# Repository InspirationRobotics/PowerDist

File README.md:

# PowerDist

`kicad` holds the kicad project / gerber files for the board, and `Power_dist` holds the code running on the microcontroller that actually does the 
hot-swapping.

The [BOM](https://docs.google.com/spreadsheets/d/1eEv6u52QYOC_kODey6bpNA8GYwr_zVqGhBdzeqPN1tI/edit?usp=sharing) holds all the internal component references 
that are in the kicad project i.e. component '1,1' is a 102k 0603 resistor. 

The [datasheet](https://docs.google.com/document/d/1oroizqdIsIZM1mA43HTIwGpKUFsHDlDQZaLfoY1nW0c/edit) for the board holds some useful information about the 
board capabilities and issues.

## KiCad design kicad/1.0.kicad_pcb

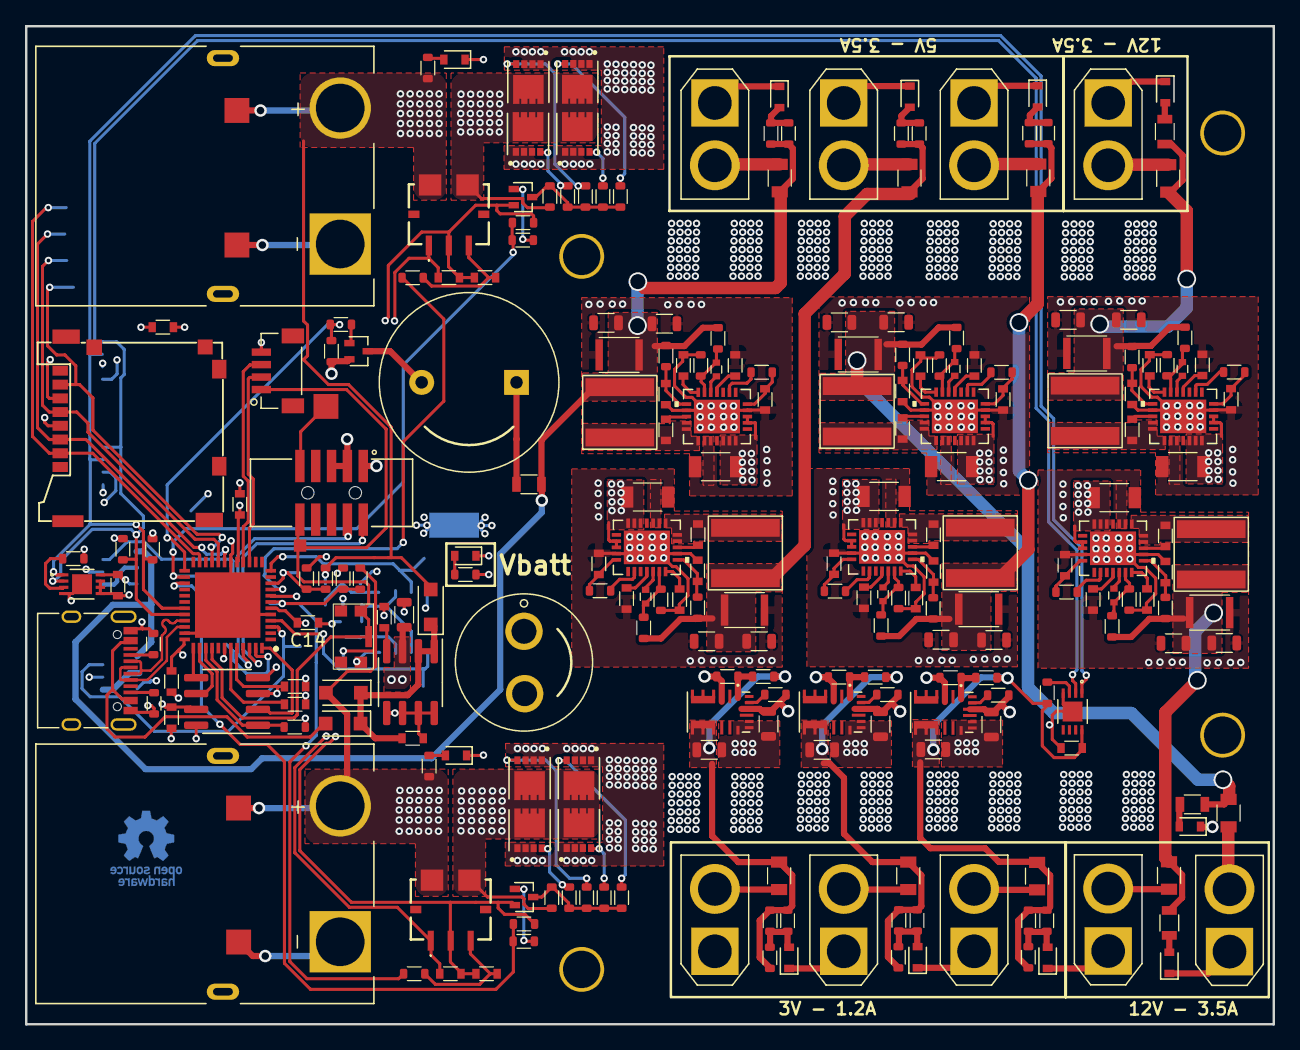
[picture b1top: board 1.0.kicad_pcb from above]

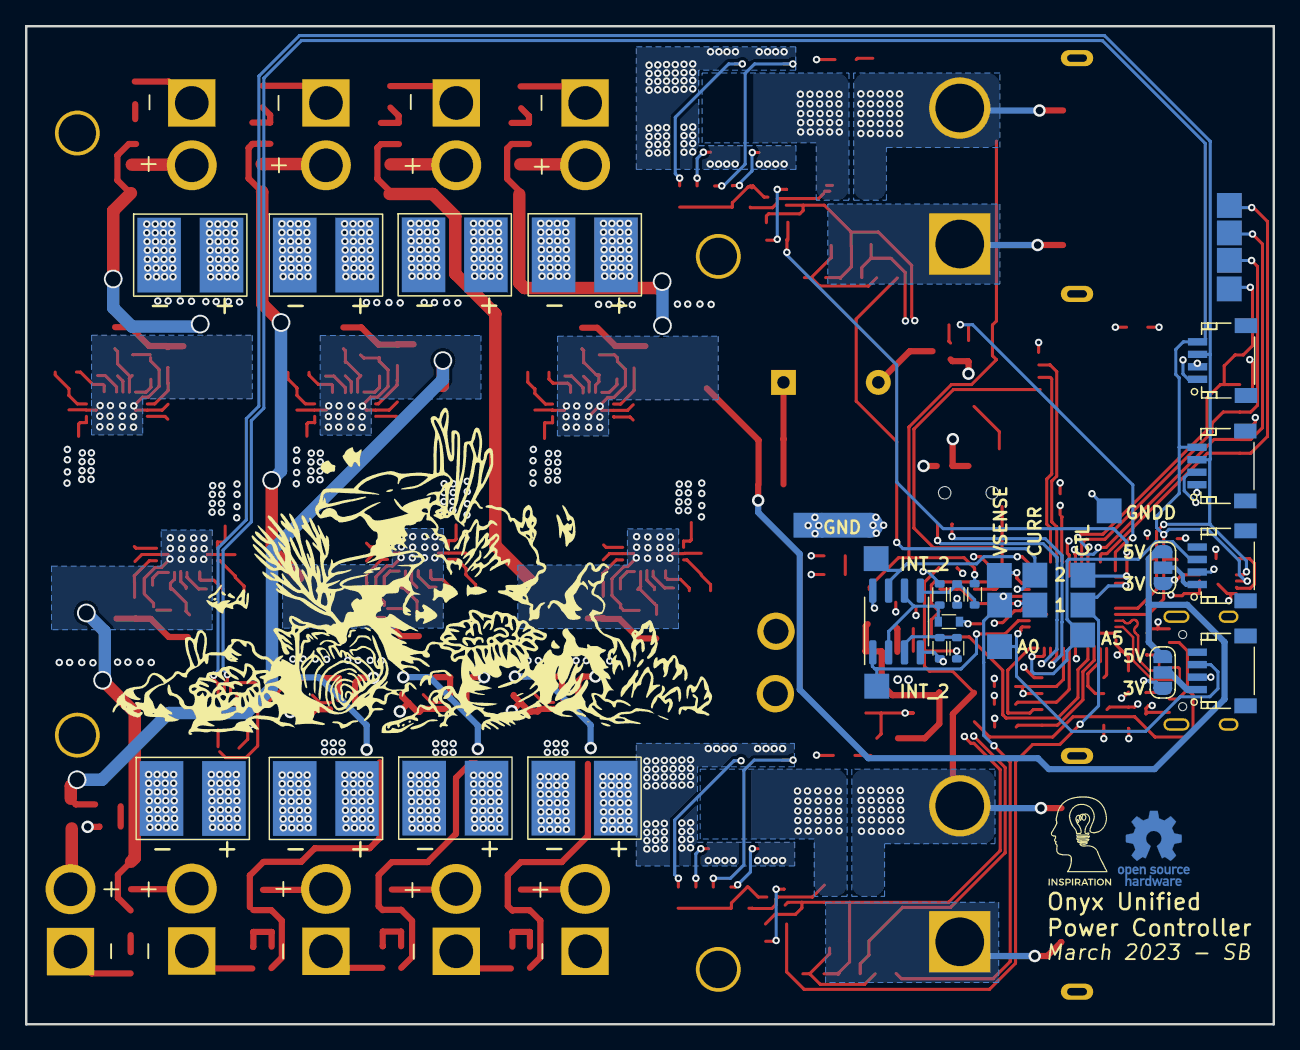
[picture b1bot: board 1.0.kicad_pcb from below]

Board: 4 copper layers, 100.0 x 80.0 mm, 290 parts (39 on the bottom side), 157 nets.

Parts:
C1, C3, C7, C9, C10, C14, C17, C29, C30, C32, C35, C37, C38, C41, C43, C65, C66, C67, C68, C69, C72, C81: 0.1u; C_1608_603_B
C2, C4, C8, C33: 1u; C_1608_603_B
C5: 470u; THT_470uF_Cap
C6, C21, C42, C47, C52, C58: 22u; C_3225_1210_B
C11, C12, C13, C15, C16, C20, C22, C26, C48, C50, C51, C56, C57, C74, C75, C80: 10u; C_2012_805_B
C18, C19, C24, C53, C54, C55: 4u7; C_3216_1206_A
C23, C25, C28, C59, C60, C61: 2u2; C_1608_603_B
C27, C31, C36, C62, C63, C64: 5n6; C_1608_603_B
C34: 100p; C_1608_603_B
C39, C40, C45, C70, C71, C73: OPEN; C_1005_402_A
C44, C46, C49: 47u; C_2012_805_B
D1, D2, D12: D_Schottky; D_SOD-123F
D3, D4, D5, D6, D7, D8, D9, D10, D11, D14, D15, D16: LED; D_0603
F1, F2, F3, F4, F5, F6, F7, F8, F9: Polyfuse_Small; R_2012_805_A
IC1: GD25Q16CWIGR; SOIC-8_3.9x4.9mm_P1.27mm
IC2: ATSAMD21G18A-MUT; QFN50P700X700X90-49N-D
J1: header_01x04; Stemma_QT_V
J3, J4, J5, J6: header_01x04; Stemma_QT_2
J7: uSDCard; uSDCard_SD_503182_011
JP1, JP2: Jumper_NO_Dual; SolderJumper-3_P1.3mm_Open_RoundedPad1.0x1.5mm_NumberLabels
L1, L2, L3: 6u8; XGL6060
L4, L5, L6: 15u; XGL6060
NT1: net-tie; NetTie-2_SMD_Pad2.0mm
P7: CONN_1; OSHW-Logo_5.7x6mm_Copper
Q1, Q2, Q7: Q_NMOS_GSD; SOT-323FL
Q3, Q4, Q5, Q6, Q9, Q10, Q11, Q12: PMOS_SGD; VDFN-8
R1, R2, R4, R6, R23, R48, R49, R53, R67, R80, R82, R84, R90, R92, R94: 10k; R_1608_603_B
R3, R52, R73, R81, R83, R85, R99: 40k2; C_1608_603_B
R5, R9, R15: 470; R_1608_603_B
R7, R18, R20, R24, R26, R50, R97, R98: 4k7; R_1608_603_B
R8, R10: 5k1; R_1608_603_B
R11, R27, R74, R77, R79, R96: 28k; R_1608_603_B
R12, R13, R14, R21, R22, R28, R54, R55, R56, R57: 1k; R_1608_603_B
R16, R25, R38, R39, R40, R41, R42, R43, R44, R45, R46, R47, R58, R59, R60, R61, R62, R63: 300; R_1608_603_B
R17, R19: 22k; R_1608_603_B
R29, R30, R31: 75k; R_1608_603_B
R32, R34, R36: 102k; R_1608_603_B
R33, R35, R37: 32.4k; R_1608_603_B
R51, R68, R69, R70: 500; R_2012_805_B
R66, R71, R75, R86, R87, R88: 4.7; R_1608_603_B
R72, R76, R78: 127k; R_1608_603_B
R89, R91, R93: 124k; R_1608_603_B
SP1: buzzer; 13-9mm_Buzzer
SW1: SW_Push; KMR243GLFG
TP1: TEST; test_point_1.0mm_square
TP2, TP3, TP4, TP5, TP6, TP7, TP8, TP9, TP10, TP11, TP12, TP13, TP14, TP15, TP16, TP17, TP18, TP19, TP20, TP21, TP22: TEST; test_point_2mm_square
U1: ARM-SWD-10
U2, U3: ACS781; 7-LR-PSOF
U4, U5, U6: MPM3610; 20-PowerLQFN
U7, U8, U27, U28: Mounting-holes; plated_hole_3.0x3.6mm
U9, U11, U12, U29, U30, U31: MAX17573; 24_WFQFN
U10: USB_C_2.0; USB_C_XKB_U262-16XN-4BVC11
U13, U14: PCT2075; PCT2075TP_147
U15, U16: XT90PW-M; AMASS_XT90PW-M_Horizontal
U17, U18, U19, U20, U21, U22, U23, U24, U25: XT30_V; AMASS_XT30U-F_1x02_P5.0mm_Vertical
U26, U32, U33, U35, U36, U37, U38, U39: ESC_CONN; 5x3.5x2mm_smd_pad
U34: AP2213-8_SOIC; SOIC-8_3.9x4.9mm_P1.27mm
U42: SOIC-8_3.9x4.9mm_P1.27mm

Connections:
3-3V_1: C15.2, C29.2, F1.2, R32.1, R38.1, R39.1, R40.1, R48.2, U4.9 (OUT), U13.8 (VCC)
3-3V_2: C16.2, F2.2, R34.1, R41.1, R42.1, R43.1, U5.9 (OUT)
3-3V_3: C22.2, F3.2, R16.1, R36.1, R58.1, R59.1, U6.9 (OUT)
5V_1: C42.2, C46.2, C50.2, F4.2, JP1.3, JP2.3, L1.2, R44.1, R45.1, R51.1, R66.1, R72.2
5V_2: C6.2, C44.2, C48.2, F5.2, L2.2, R46.1, R47.1, R71.1, R76.2
5V_3: C47.2, C49.2, C51.2, F6.2, L3.2, R60.1, R61.1, R75.1, R78.2
12V_1: C20.2, C21.2, C26.2, F7.2, L4.2, R68.2, R86.1, R89.2
12V_2: C52.2, C56.2, C57.2, F8.2, L5.2, R69.2, R87.1, R91.2
12V_3: C58.2, C74.2, C75.2, F9.2, L6.2, R70.2, R88.1, R93.2
+3V3: C1.2, C3.2, C7.2, C9.2, C10.2, C14.2, C17.2, C30.2, C80.2, C81.2, IC1.3 (~WP_(IO2)), IC1.7 (~HOLD_(IO3)), IC1.8 (VCC), IC2.6 (VDDANA), IC2.17 (VDDIO_1), IC2.36 (VDDIO_2), IC2.44 (VDDIN), J5.2, J6.2, J7.4 (VDD), JP1.1, JP2.1, R1.1, R53.2, R96.2, R97.2, R98.2, U1.1 (Vref), U2.1 (VCC), U3.1 (VCC), U14.8 (VCC), U34.3 (VOUT), U42.8 (V+)
+BATT: C5.1, C11.1, C12.1, C13.1, C18.1, C19.1, C24.1, C53.1, C54.1, C55.1, Q3.1 (S), Q4.1 (S), Q5.1 (S), Q6.1 (S), Q9.1 (S), Q10.1 (S), Q11.1 (S), Q12.1 (S), R15.1, R29.1, R30.1, R31.1, U4.16 (IN), U5.16 (IN), U6.16 (IN), U9.5 (IN), U9.6 (IN), U9.7 (IN), U9.9 (IN), U9.10 (EN/UVLO), U11.5 (IN), U11.6 (IN), U11.7 (IN), U11.9 (IN), U11.10 (EN/UVLO), U12.5 (IN), U12.6 (IN), U12.7 (IN), U12.9 (IN), U12.10 (EN/UVLO), U26.2 (+), U29.5 (IN), U29.6 (IN), U29.7 (IN), U29.9 (IN), U29.10 (EN/UVLO), U30.5 (IN), U30.6 (IN), U30.7 (IN), U30.9 (IN), U30.10 (EN/UVLO), U31.5 (IN), U31.6 (IN), U31.7 (IN), U31.9 (IN), U31.10 (EN/UVLO), U32.2 (+), U33.2 (+), U35.2 (+), U36.2 (+), U37.2 (+), U38.2 (+), U39.2 (+)
/A0_SENSE: IC2.3 (PA02), J4.3, TP7.1
/A5_SENSE: IC2.47 (PB02), J3.3, TP15.1
/BUZZER: IC2.25 (PA16), R49.2, R63.2
/MISO: IC2.21 (PA12), J7.7 (DOUT), TP9.1
/MOSI: IC2.19 (PB10), J7.3 (DIN), TP5.1
/SCK: IC2.20 (PB11), J7.5 (SCLK), TP6.1
/SCL: IC2.32 (PA23), J5.4, J6.4, R98.1, U13.2 (SCL), U14.2 (SCL)
/SDA: IC2.31 (PA22), J5.3, J6.3, R97.1, U13.1 (SDA), U14.1 (SDA)
/SD_CS: IC2.23 (PA14), J7.2 (CS), TP10.1
/SERIAL1_RX: IC2.16 (PA11), J1.3
/SERIAL1_TX: IC2.15 (PA10), J1.2
/SWCLK: IC2.45 (PA30), U1.4 (SWDCLK/TCK)
/SWDIO: IC2.46 (PA31), U1.2 (SWDIO/TMS)
/USB_D+: IC2.34 (PA25), U10.A6 (D+), U10.B6 (D+)
/USB_D-: IC2.33 (PA24), U10.A7 (D-), U10.B7 (D-)
/batt_ctl/BATT_1_CTL: IC2.27 (PA18), R6.2, R25.2, TP11.1
/batt_ctl/BATT_1_CURR: IC2.8 (PB09), R7.1, TP4.1
/batt_ctl/BATT_1_INT: IC2.4 (PA03), TP21.1, U42.1 (A)
/batt_ctl/BATT_1_VSENSE: IC2.7 (PB08), R17.2, R18.1, TP3.1
/batt_ctl/BATT_2_CTL: IC2.26 (PA17), R23.2, R62.1, TP14.1
/batt_ctl/BATT_2_CURR: IC2.9 (PA04), R24.1, TP12.1
/batt_ctl/BATT_2_INT: IC2.12 (PA07), TP22.1, U42.7 (B)
/batt_ctl/BATT_2_VSENSE: IC2.10 (PA05), R19.2, R20.1, TP8.1
/processor/FLASH_CS: IC1.1 (~CS), IC2.39 (PA27), R1.2
/processor/FLASH_MISO: IC1.2 (SO_(IO1)), IC2.48 (PB03)
/processor/FLASH_MOSI: IC1.5 (SI_(IO0)), IC2.37 (PB22)
/processor/FLASH_SCK: IC1.6 (SCLK), IC2.38 (PB23)
/~RESET_RAW: IC2.40 (~RESET), J1.1, SW1.1, TP1.1, U1.10 (~RESET)
BATT_1_PWR: D2.2 (A), R5.1, R17.1, R27.2, TP17.1, U2.6 (IP-), U15.2 (+)
BATT_2_PWR: D12.2 (A), R9.1, R11.2, R19.1, TP18.1, U3.6 (IP-), U16.2 (+)
GND: C5.2, C6.1, C11.2, C12.2, C13.2, C15.1, C16.1, C18.2, C19.2, C20.1, C21.1, C22.1, C23.2, C24.2, C25.2, C26.1, C27.2, C28.2, C29.1, C31.2, C32.1, C35.1, C36.2, C41.1, C42.1, C44.1, C46.1, C47.1, C48.1, C49.1, C50.1, C51.1, C52.1, C53.2, C54.2, C55.2, C56.1, C57.1, C58.1, C59.2, C60.2, C61.2, C62.2, C63.2, C64.2, C65.1, C66.1, C67.1, C74.1, C75.1, D3.1 (K), D4.1 (K), D5.1 (K), D6.1 (K), D7.1 (K), D8.1 (K), D9.1 (K), D10.1 (K), D11.1 (K), D14.1 (K), D15.1 (K), D16.1 (K), NT1.2, R3.2, R33.2, R35.2, R37.2, R52.2, R73.2, R74.1, R77.1, R79.1, R81.2, R83.2, R85.2, R90.2, R92.2, R94.2, TP16.1, TP19.1, TP20.1, U4.3 (AGND), U4.12 (PGND), U4.13 (PGND), U4.14 (PGND), U5.3 (AGND), U5.12 (PGND), U5.13 (PGND), U5.14 (PGND), U6.3 (AGND), U6.12 (PGND), U6.13 (PGND), U6.14 (PGND), U9.2 (PGND), U9.3 (PGND), U9.11 (PGND), U9.21 (SGND), U9.25 (EP), U11.2 (PGND), U11.3 (PGND), U11.11 (PGND), U11.21 (SGND), U11.25 (EP), U12.2 (PGND), U12.3 (PGND), U12.11 (PGND), U12.21 (SGND), U12.25 (EP), U13.4 (GND), U13.9 (EP_GND), U15.1 (-), U16.1 (-), U17.1 (-), U18.1 (-), U19.1 (-), U20.1 (-), U21.1 (-), U22.1 (-), U23.1 (-), U24.1 (-), U25.1 (-), U26.1 (-), U29.2 (PGND), U29.3 (PGND), U29.11 (PGND), U29.21 (SGND), U29.25 (EP), U30.2 (PGND), U30.3 (PGND), U30.11 (PGND), U30.21 (SGND), U30.25 (EP), U31.2 (PGND), U31.3 (PGND), U31.11 (PGND), U31.21 (SGND), U31.25 (EP), U32.1 (-), U33.1 (-), U35.1 (-), U36.1 (-), U37.1 (-), U38.1 (-), U39.1 (-)
GNDD: C1.1, C2.2, C3.1, C4.1, C7.1, C8.1, C9.1, C10.1, C14.1, C17.1, C30.1, C33.1, C34.2, C80.1, C81.1, IC1.4 (VSS), IC2.5 (GNDANA), IC2.18 (GND_1), IC2.35 (GND_2), IC2.42 (GND_3), IC2.49 (EP_GND), J1.4, J3.2, J4.2, J5.1, J6.1, J7.6 (GND), NT1.1, Q1.2 (S), Q2.2 (S), Q7.2 (S), R6.1, R8.1, R10.2, R18.2, R20.2, R23.1, R26.2, R49.1, R50.2, R99.2, SW1.3, TP13.1, U1.3 (GND), U1.5 (GND), U2.2 (GND), U3.2 (GND), U10.A1 (GND), U10.A12 (GND), U10.B1 (GND), U10.B12 (GND), U10.S1 (SHIELD), U14.4 (GND), U14.5 (A2), U14.6 (A1), U14.7 (A0), U14.9 (EP_GND), U34.5 (GND), U34.6 (GND), U34.7 (GND), U34.8 (GND), U42.4 (V-)
unnamed: C2.1, IC2.43 (VDDCORE)
unnamed: C41.2, R75.2, U12.20 (EXTVCC)
unnamed: C33.2, D1.1 (K), D2.1 (K), D12.1 (K), U34.1 (EN), U34.2 (VIN)
unnamed: C66.2, R87.2, U30.20 (EXTVCC)
unnamed: C65.2, R86.2, U29.20 (EXTVCC)
unnamed: C67.2, R88.2, U31.20 (EXTVCC)
unnamed: C32.2, R66.2, U9.20 (EXTVCC)
unnamed: C35.2, R71.2, U11.20 (EXTVCC)
unnamed: C37.1, L1.1, U9.1 (LX), U9.23 (LX), U9.24 (LX)
unnamed: C38.1, L2.1, U11.1 (LX), U11.23 (LX), U11.24 (LX)
unnamed: C43.1, L3.1, U12.1 (LX), U12.23 (LX), U12.24 (LX)
unnamed: C68.1, L4.1, U29.1 (LX), U29.23 (LX), U29.24 (LX)
unnamed: C69.1, L5.1, U30.1 (LX), U30.23 (LX), U30.24 (LX)
unnamed: C72.1, L6.1, U31.1 (LX), U31.23 (LX), U31.24 (LX)
unnamed: D3.2 (A), R5.2
unnamed: D4.2 (A), R9.2
unnamed: D5.2 (A), R15.2
unnamed: D6.2 (A), R16.2, R58.2, R59.2
unnamed: D7.2 (A), R38.2, R39.2, R40.2
unnamed: D8.2 (A), R41.2, R42.2, R43.2
unnamed: D9.2 (A), R44.2, R45.2
unnamed: D10.2 (A), R46.2, R47.2
unnamed: D11.2 (A), R60.2, R61.2
unnamed: D14.2 (A), R68.1
unnamed: D15.2 (A), R69.1
unnamed: D16.2 (A), R70.1
unnamed: J3.1, JP1.2
unnamed: J4.1, JP2.2
unnamed: Q1.3 (D), R12.1, R13.2, R14.2, R21.2, R22.2
unnamed: Q1.1 (G), R25.1
unnamed: Q2.3 (D), R28.1, R54.2, R55.2, R56.2, R57.2
unnamed: Q2.1 (G), R62.2
unnamed: Q3.3 (D), Q4.3 (D), Q5.3 (D), Q6.3 (D), R12.2, U2.5 (IP+)
unnamed: Q3.2 (G), R13.1
unnamed: Q4.2 (G), R14.1
unnamed: Q5.2 (G), R21.1
unnamed: Q6.2 (G), R22.1
unnamed: Q7.3 (D), SP1.2 (-)
unnamed: Q7.1 (G), R63.1
unnamed: Q9.2 (G), R54.1
unnamed: Q9.3 (D), Q10.3 (D), Q11.3 (D), Q12.3 (D), R28.2, U3.5 (IP+)
unnamed: Q10.2 (G), R55.1
unnamed: Q11.2 (G), R56.1
unnamed: Q12.2 (G), R57.1
unnamed: R51.2, SP1.1 (+)
unnamed: TP2.1, U1.9 (GNDDetect)
unnamed: C4.2, R7.2, U2.3 (VOUT)
unnamed: C8.2, R24.2, U3.3 (VOUT)
unnamed: R29.2, U4.17 (EN)
unnamed: R32.2, R33.1, U4.1 (FB)
unnamed: R30.2, U5.17 (EN)
unnamed: R34.2, R35.1, U5.1 (FB)
unnamed: R31.2, U6.17 (EN)
unnamed: R36.2, R37.1, U6.1 (FB)
unnamed: C37.2, U9.22 (BST)
unnamed: C39.2, U9.17 (CF)
unnamed: C39.1, R72.1, R74.2, U9.18 (FB)
unnamed: R3.1, U9.19 (RT)
unnamed: C27.1, U9.16 (SS)
unnamed: C23.1, R2.2, U9.12 (VCC)
unnamed: R2.1, U9.14 (~RESET)
unnamed: R10.1, U10.A5 (CC1)
unnamed: R8.2, U10.B5 (CC2)
unnamed: C38.2, U11.22 (BST)
unnamed: C40.2, U11.17 (CF)
unnamed: C40.1, R76.1, R77.2, U11.18 (FB)
unnamed: R52.1, U11.19 (RT)
unnamed: C31.1, U11.16 (SS)
unnamed: C25.1, R4.2, U11.12 (VCC)
unnamed: R4.1, U11.14 (~RESET)
unnamed: C43.2, U12.22 (BST)
unnamed: C45.2, U12.17 (CF)
unnamed: C45.1, R78.1, R79.2, U12.18 (FB)
unnamed: R73.1, U12.19 (RT)
unnamed: C36.1, U12.16 (SS)
unnamed: C28.1, R67.2, U12.12 (VCC)
unnamed: R67.1, U12.14 (~RESET)
unnamed: R48.1, U13.3 (OS)
unnamed: R53.1, U14.3 (OS)
unnamed: F1.1, U17.2 (+)
unnamed: F2.1, U18.2 (+)
unnamed: F3.1, U19.2 (+)
unnamed: F4.1, U20.2 (+)
unnamed: F5.1, U21.2 (+)
unnamed: F6.1, U22.2 (+)
unnamed: F7.1, U23.2 (+)
unnamed: F8.1, U24.2 (+)
unnamed: F9.1, U25.2 (+)
unnamed: C68.2, U29.22 (BST)
unnamed: C71.2, U29.17 (CF)
unnamed: C71.1, R89.1, R90.1, U29.18 (FB)
unnamed: R81.1, U29.19 (RT)
unnamed: C62.1, U29.16 (SS)
unnamed: C59.1, R80.2, U29.12 (VCC)
unnamed: R80.1, U29.14 (~RESET)
unnamed: C69.2, U30.22 (BST)
unnamed: C70.2, U30.17 (CF)
unnamed: C70.1, R91.1, R92.1, U30.18 (FB)
unnamed: R83.1, U30.19 (RT)
unnamed: C63.1, U30.16 (SS)
unnamed: C60.1, R82.2, U30.12 (VCC)
unnamed: R82.1, U30.14 (~RESET)
unnamed: C72.2, U31.22 (BST)
unnamed: C73.2, U31.17 (CF)
unnamed: C73.1, R93.1, R94.1, U31.18 (FB)
unnamed: R85.1, U31.19 (RT)
unnamed: C64.1, U31.16 (SS)
unnamed: C61.1, R84.2, U31.12 (VCC)
unnamed: R84.1, U31.14 (~RESET)
unnamed: C34.1, U34.4 (BYP)
unnamed: R27.1, R50.1, U42.3 (A+)
unnamed: R96.1, R99.1, U42.2 (A-), U42.6 (B-)
unnamed: R11.1, R26.1, U42.5 (B+)
VUSB: D1.2 (A), U10.A4 (VBUS), U10.A9 (VBUS), U10.B4 (VBUS), U10.B9 (VBUS)

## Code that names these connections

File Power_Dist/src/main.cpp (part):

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#define ALLOW_SERIAL_DEBUG

// Pin Definitions
#define BATT_1_VSENSE A1
#define BATT_1_CURR 2
#define BATT_1_INT 4
#define BATT_1_CTL 10

#define BATT_2_VSENSE A4
#define BATT_2_CURR A3
#define BATT_2_INT 9
#define BATT_2_CTL 13

#define A0_SENSE A0
#define A5_SENSE A5
#define BUZZER 11
#define SD_CS 2
#define SERIAL_1_RX 0
#define SERIAL_1_TX 1

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  //   ;
  // }

  pinMode(BATT_1_VSENSE, INPUT_PULLDOWN);
  pinMode(BATT_1_CURR, INPUT_PULLDOWN);
  pinMode(BATT_1_INT, INPUT_PULLUP);
  pinMode(BATT_1_CTL, OUTPUT);

  pinMode(BATT_2_VSENSE, INPUT_PULLDOWN);
  pinMode(BATT_2_CURR, INPUT_PULLDOWN);
  pinMode(BATT_2_INT, INPUT_PULLUP);
  pinMode(BATT_2_CTL, OUTPUT);

  pinMode(A0_SENSE, INPUT);
  pinMode(A5_SENSE, INPUT);
  pinMode(SERIAL_1_RX, INPUT_PULLUP);

  // attachInterrupt(digitalPinToInterrupt(BATT_1_INT), batt1ISR, FALLING);
  // attachInterrupt(digitalPinToInterrupt(BATT_2_INT), batt2ISR, FALLING);

  batt1On = false;
  batt2On = false;
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  batt2Curr = 0;
  prevCurrSense = micros();
  for (int x = 0; x < sizeof(batt1VFIFO) / sizeof(float); x++) {
    batt1VFIFO[x] = getPinVolt(BATT_1_CURR);
    batt2VFIFO[x] = getPinVolt(BATT_2_CURR);
  }


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}

void pollBatteries() {
  batt1V = calcVBatt(getPinVolt(BATT_1_VSENSE));
  batt2V = calcVBatt(getPinVolt(BATT_2_VSENSE));

  batt1Installed = batt1V > 0.5;
  batt2Installed = batt2V > 0.5;
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      batt1Sum += batt1VFIFO[x];
      batt2Sum += batt2VFIFO[x];
    }
    batt1VFIFO[0] = getPinVolt(BATT_1_CURR);
    batt2VFIFO[0] = getPinVolt(BATT_2_CURR);
    batt1Sum += batt1VFIFO[0];
    batt2Sum += batt2VFIFO[0];

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
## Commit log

2023-05-07 Thermometers
2023-05-08 initial
2023-05-14 switching working, adding interrupts
2023-05-14 added interrupts and buzzer, untested
2023-05-17 loop switching working, errors untested
2023-05-17 added gerbers
2023-05-17 readme updates
2023-05-17 timer testing
2023-05-17 working final
2023-05-17 final
2023-06-04 arming / disarming
2023-06-04 setting changes
2023-06-05 latest
2023-06-12 hlc serial data parser
2023-06-14 current sense updates
2023-06-14 Added serial comms flags
2023-06-14 hlc reporting added
2023-06-17 license
2023-06-23 current constant updates
2023-06-24 scripting update
